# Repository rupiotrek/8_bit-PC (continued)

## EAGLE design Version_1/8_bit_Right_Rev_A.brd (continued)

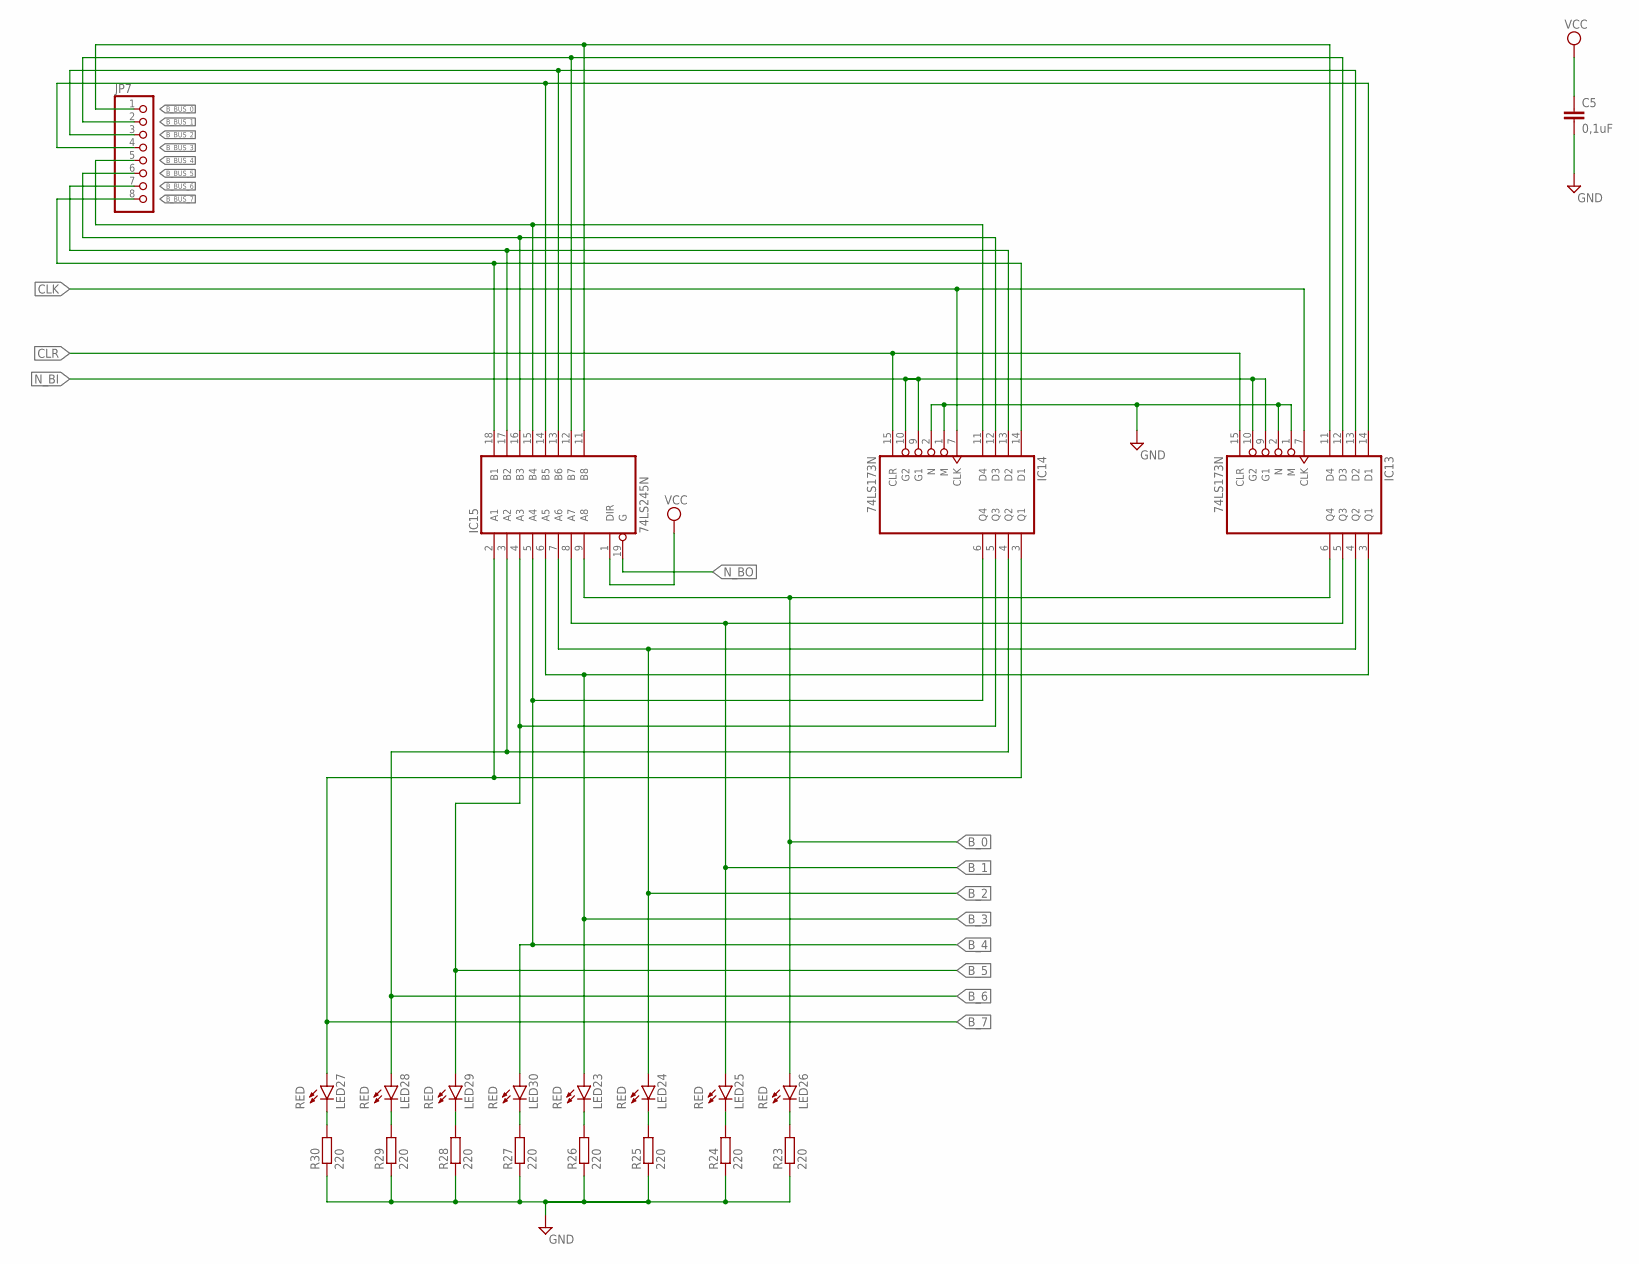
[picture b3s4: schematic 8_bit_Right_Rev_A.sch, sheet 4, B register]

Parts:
C5: 0,1uF; C025-030X050
IC13, IC14: 74LS173N; DIL16
IC15: 74LS245N; DIL20
JP7: PINHD-1X8; 1X08
LED23, LED24, LED25, LED26, LED27, LED28, LED29, LED30: RED; LED5MM
R23, R24, R25, R26, R27, R28, R29, R30: 220; 0207/10

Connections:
B_0: IC13.6 (Q4), IC15.9 (A8), LED26.A; also elsewhere on the board
B_1: IC13.5 (Q3), IC15.8 (A7), LED25.A; also elsewhere on the board
B_2: IC13.4 (Q2), IC15.7 (A6), LED24.A; also elsewhere on the board
B_3: IC13.3 (Q1), IC15.6 (A5), LED23.A; also elsewhere on the board
B_4: IC14.6 (Q4), IC15.5 (A4), LED30.A; also elsewhere on the board
B_5: IC14.5 (Q3), IC15.4 (A3), LED29.A; also elsewhere on the board
B_6: IC14.4 (Q2), IC15.3 (A2), LED28.A; also elsewhere on the board
B_7: IC14.3 (Q1), IC15.2 (A1), LED27.A; also elsewhere on the board
B_BUS_0: IC13.11 (D4), IC15.11 (B8), JP7.1
B_BUS_1: IC13.12 (D3), IC15.12 (B7), JP7.2
B_BUS_2: IC13.13 (D2), IC15.13 (B6), JP7.3
B_BUS_3: IC13.14 (D1), IC15.14 (B5), JP7.4
B_BUS_4: IC14.11 (D4), IC15.15 (B4), JP7.5
B_BUS_5: IC14.12 (D3), IC15.16 (B3), JP7.6
B_BUS_6: IC14.13 (D2), IC15.17 (B2), JP7.7
B_BUS_7: IC14.14 (D1), IC15.18 (B1), JP7.8
CLK: IC13.7 (CLK), IC14.7 (CLK); also elsewhere on the board
CLR: IC13.15 (CLR), IC14.15 (CLR); also elsewhere on the board
GND: C5.2, IC13.1 (M), IC13.2 (N), IC13.8 (GND), IC14.1 (M), IC14.2 (N), IC14.8 (GND), IC15.10 (GND), R23.1, R24.1, R25.1, R26.1, R27.1, R28.1, R29.1, R30.1; also elsewhere on the board
GND9: LED26.K (C), R23.2
GND10: LED25.K (C), R24.2
GND11: LED24.K (C), R25.2
GND12: LED23.K (C), R26.2
GND13: LED30.K (C), R27.2
GND14: LED29.K (C), R28.2
GND15: LED28.K (C), R29.2
GND16: LED27.K (C), R30.2
N_BI: IC13.9 (G1), IC13.10 (G2), IC14.9 (G1), IC14.10 (G2); also elsewhere on the board
N_BO: IC15.19 (G)
VCC: C5.1, IC13.16 (VCC), IC14.16 (VCC), IC15.1 (DIR), IC15.20 (VCC); also elsewhere on the board

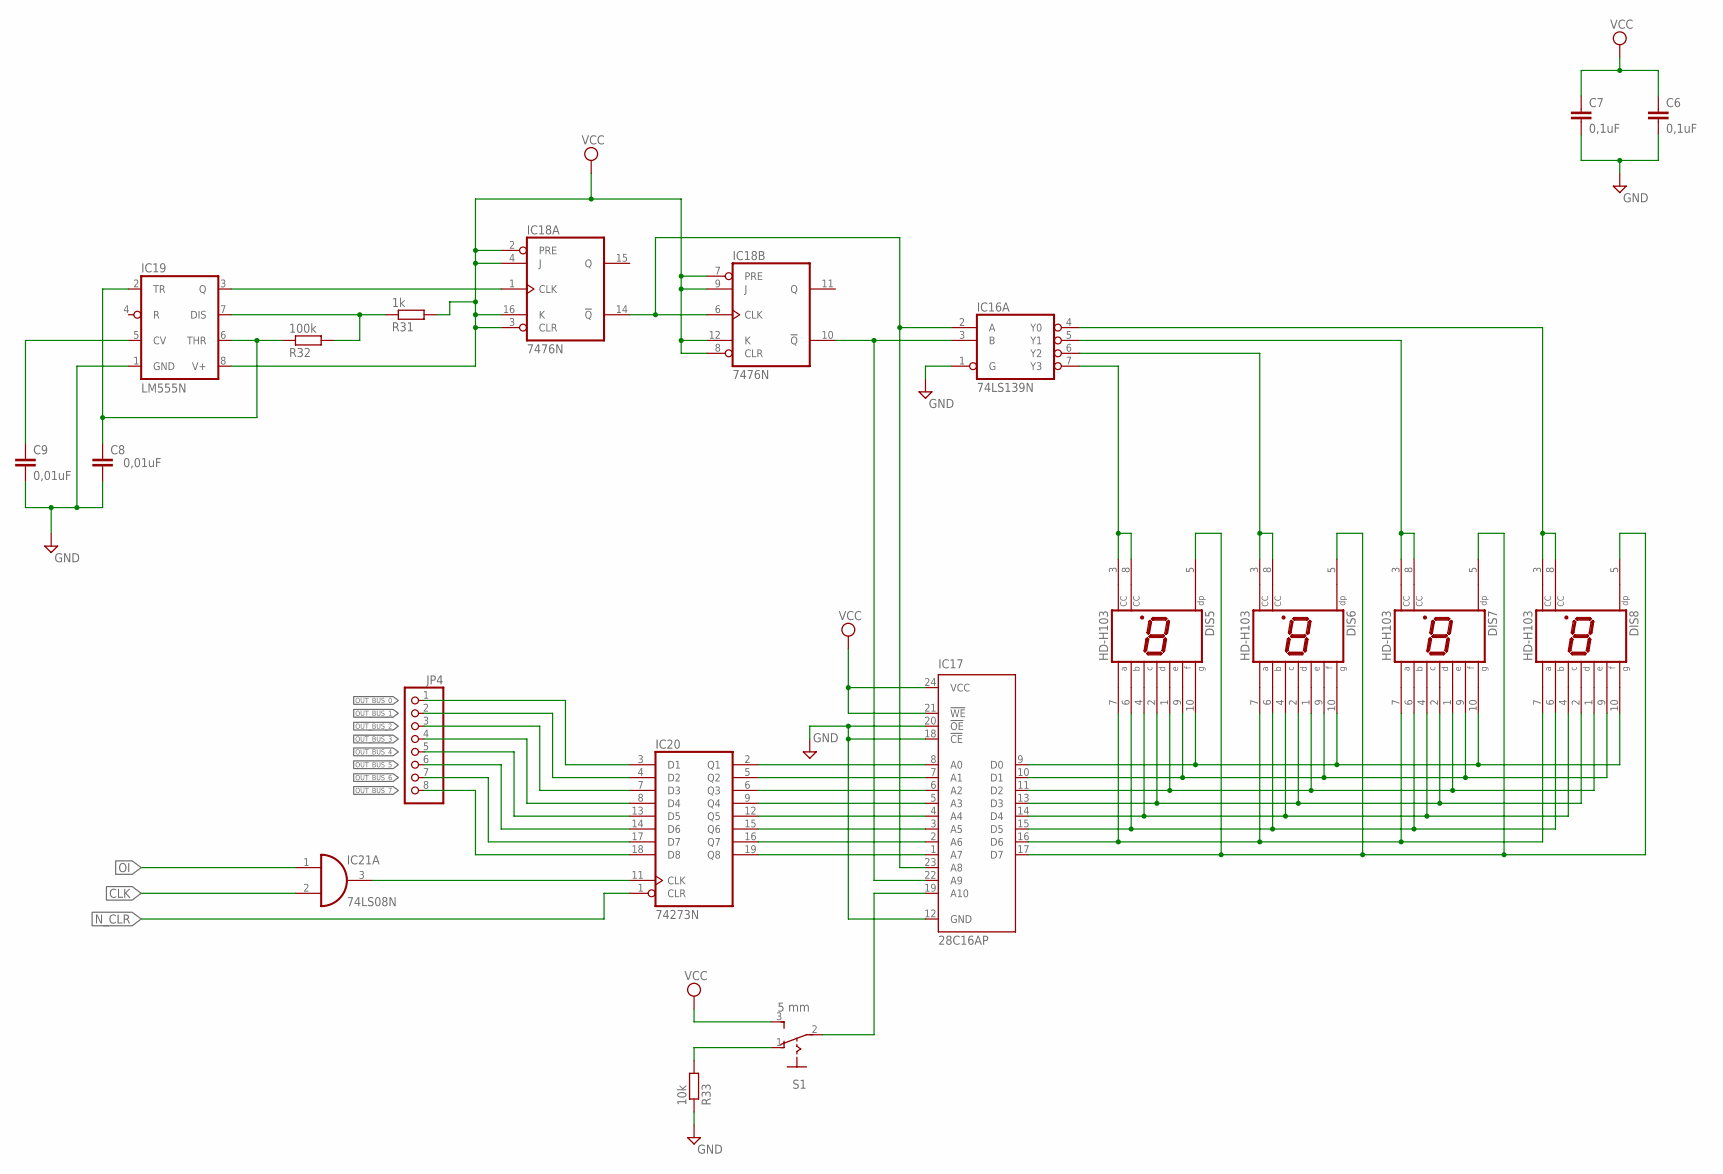
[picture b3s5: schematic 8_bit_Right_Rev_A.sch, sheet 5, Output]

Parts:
C6, C7: 0,1uF; C025-030X050
C8, C9: 0,01uF; C025-030X050
DIS5, DIS6, DIS7, DIS8: HD-H103; HDSP-M
IC16: 74LS139N; DIL16
IC17: 28C16AP; DIL24-6
IC18: 7476N; DIL16
IC19: LM555N; DIL08
IC20: 74273N; DIL20
IC21: 74LS08N; DIL14
JP4: PINHD-1X8; 1X08
R31: 1k; 0207/10
R32: 100k; 0207/10
R33: 10k; 0207/10
S1: 5 mm; 255SB

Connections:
CLK: IC21.2 (I1); also elsewhere on the board
GND: C6.2, C7.2, C8.2, C9.2, IC16.1 (G), IC16.8 (GND), IC17.12 (GND), IC17.18 (!CE), IC17.20 (!OE), IC18.13 (GND), IC19.1 (GND), IC20.10 (GND), IC21.7 (GND), R33.1; also elsewhere on the board
unnamed: IC17.8 (A0), IC20.2 (Q1)
unnamed: IC17.7 (A1), IC20.5 (Q2)
unnamed: IC17.6 (A2), IC20.6 (Q3)
unnamed: IC17.5 (A3), IC20.9 (Q4)
unnamed: IC17.4 (A4), IC20.12 (Q5)
unnamed: IC17.3 (A5), IC20.15 (Q6)
unnamed: IC17.2 (A6), IC20.16 (Q7)
unnamed: IC17.1 (A7), IC20.19 (Q8)
unnamed: DIS5.5 (DP), DIS6.5 (DP), DIS7.5 (DP), DIS8.5 (DP), IC17.17 (D7)
unnamed: DIS5.7 (A), DIS6.7 (A), DIS7.7 (A), DIS8.7 (A), IC17.16 (D6)
unnamed: DIS5.6 (B), DIS6.6 (B), DIS7.6 (B), DIS8.6 (B), IC17.15 (D5)
unnamed: DIS5.4 (C), DIS6.4 (C), DIS7.4 (C), DIS8.4 (C), IC17.14 (D4)
unnamed: DIS5.2 (D), DIS6.2 (D), DIS7.2 (D), DIS8.2 (D), IC17.13 (D3)
unnamed: DIS5.1 (E), DIS6.1 (E), DIS7.1 (E), DIS8.1 (E), IC17.11 (D2)
unnamed: DIS5.9 (F), DIS6.9 (F), DIS7.9 (F), DIS8.9 (F), IC17.10 (D1)
unnamed: DIS5.10 (G), DIS6.10 (G), DIS7.10 (G), DIS8.10 (G), IC17.9 (D0)
unnamed: DIS5.3 (CC), DIS5.8 (CC), IC16.7 (Y3)
unnamed: DIS6.3 (CC), DIS6.8 (CC), IC16.6 (Y2)
unnamed: DIS7.3 (CC), DIS7.8 (CC), IC16.5 (Y1)
unnamed: DIS8.3 (CC), DIS8.8 (CC), IC16.4 (Y0)
unnamed: IC16.3 (B), IC17.22 (A9), IC18.10 (!Q)
unnamed: IC16.2 (A), IC17.23 (A8), IC18.6 (CLK), IC18.14 (!Q)
unnamed: IC18.1 (CLK), IC19.3 (Q)
unnamed: IC19.7 (DIS), R31.1, R32.2
unnamed: C8.1, IC19.2 (TR), IC19.6 (THR), R32.1
unnamed: C9.1, IC19.5 (CV)
unnamed: IC20.11 (CLK), IC21.3 (O)
unnamed: IC17.19 (A10), S1.2
unnamed: R33.2, S1.1 (O)
N_CLR: IC20.1 (CLR); also elsewhere on the board
OI: IC21.1 (I0); also elsewhere on the board
OUT_BUS_0: IC20.3 (D1), JP4.1
OUT_BUS_1: IC20.4 (D2), JP4.2
OUT_BUS_2: IC20.7 (D3), JP4.3
OUT_BUS_3: IC20.8 (D4), JP4.4
OUT_BUS_4: IC20.13 (D5), JP4.5
OUT_BUS_5: IC20.14 (D6), JP4.6
OUT_BUS_6: IC20.17 (D7), JP4.7
OUT_BUS_7: IC20.18 (D8), JP4.8
VCC: C6.1, C7.1, IC16.16 (VCC), IC17.21 (!WE), IC17.24 (VCC), IC18.2 (PRE), IC18.3 (CLR), IC18.4 (J), IC18.5 (VCC), IC18.7 (PRE), IC18.8 (CLR), IC18.9 (J), IC18.12 (K), IC18.16 (K), IC19.8 (V+), IC20.20 (VCC), IC21.14 (VCC), R31.2, S1.3 (S); also elsewhere on the board

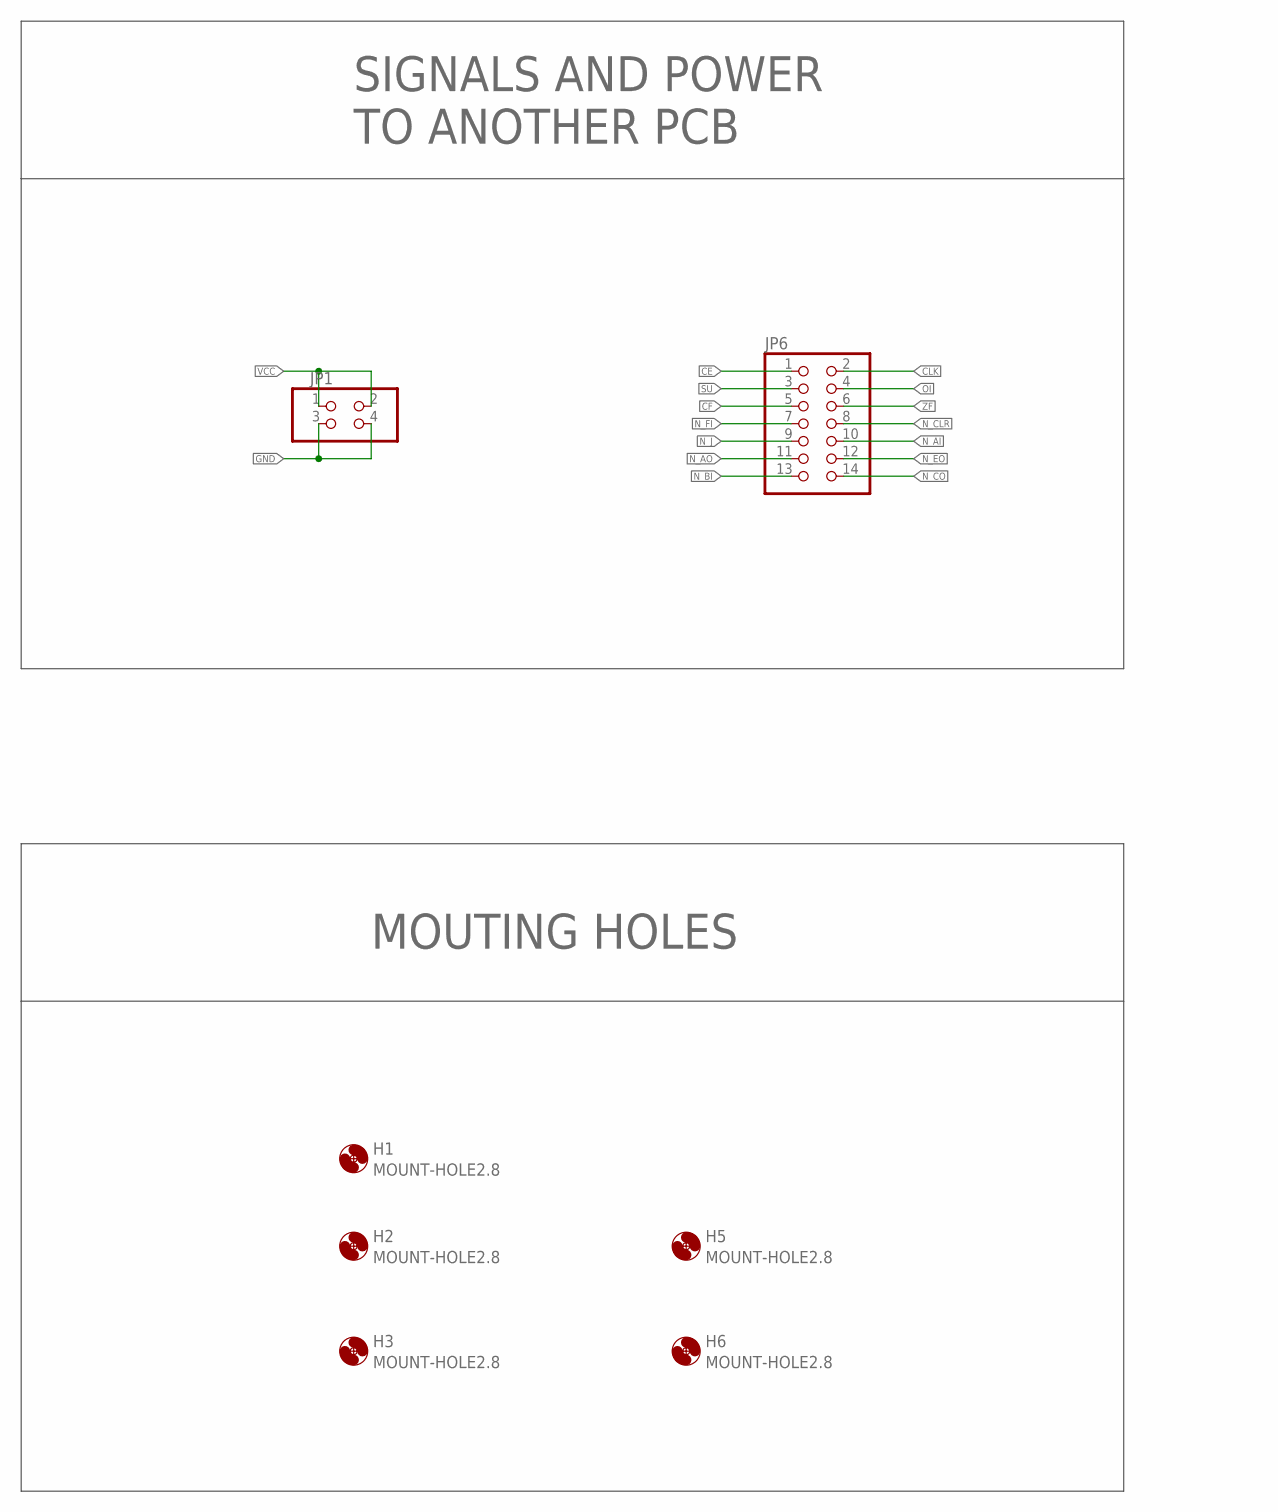
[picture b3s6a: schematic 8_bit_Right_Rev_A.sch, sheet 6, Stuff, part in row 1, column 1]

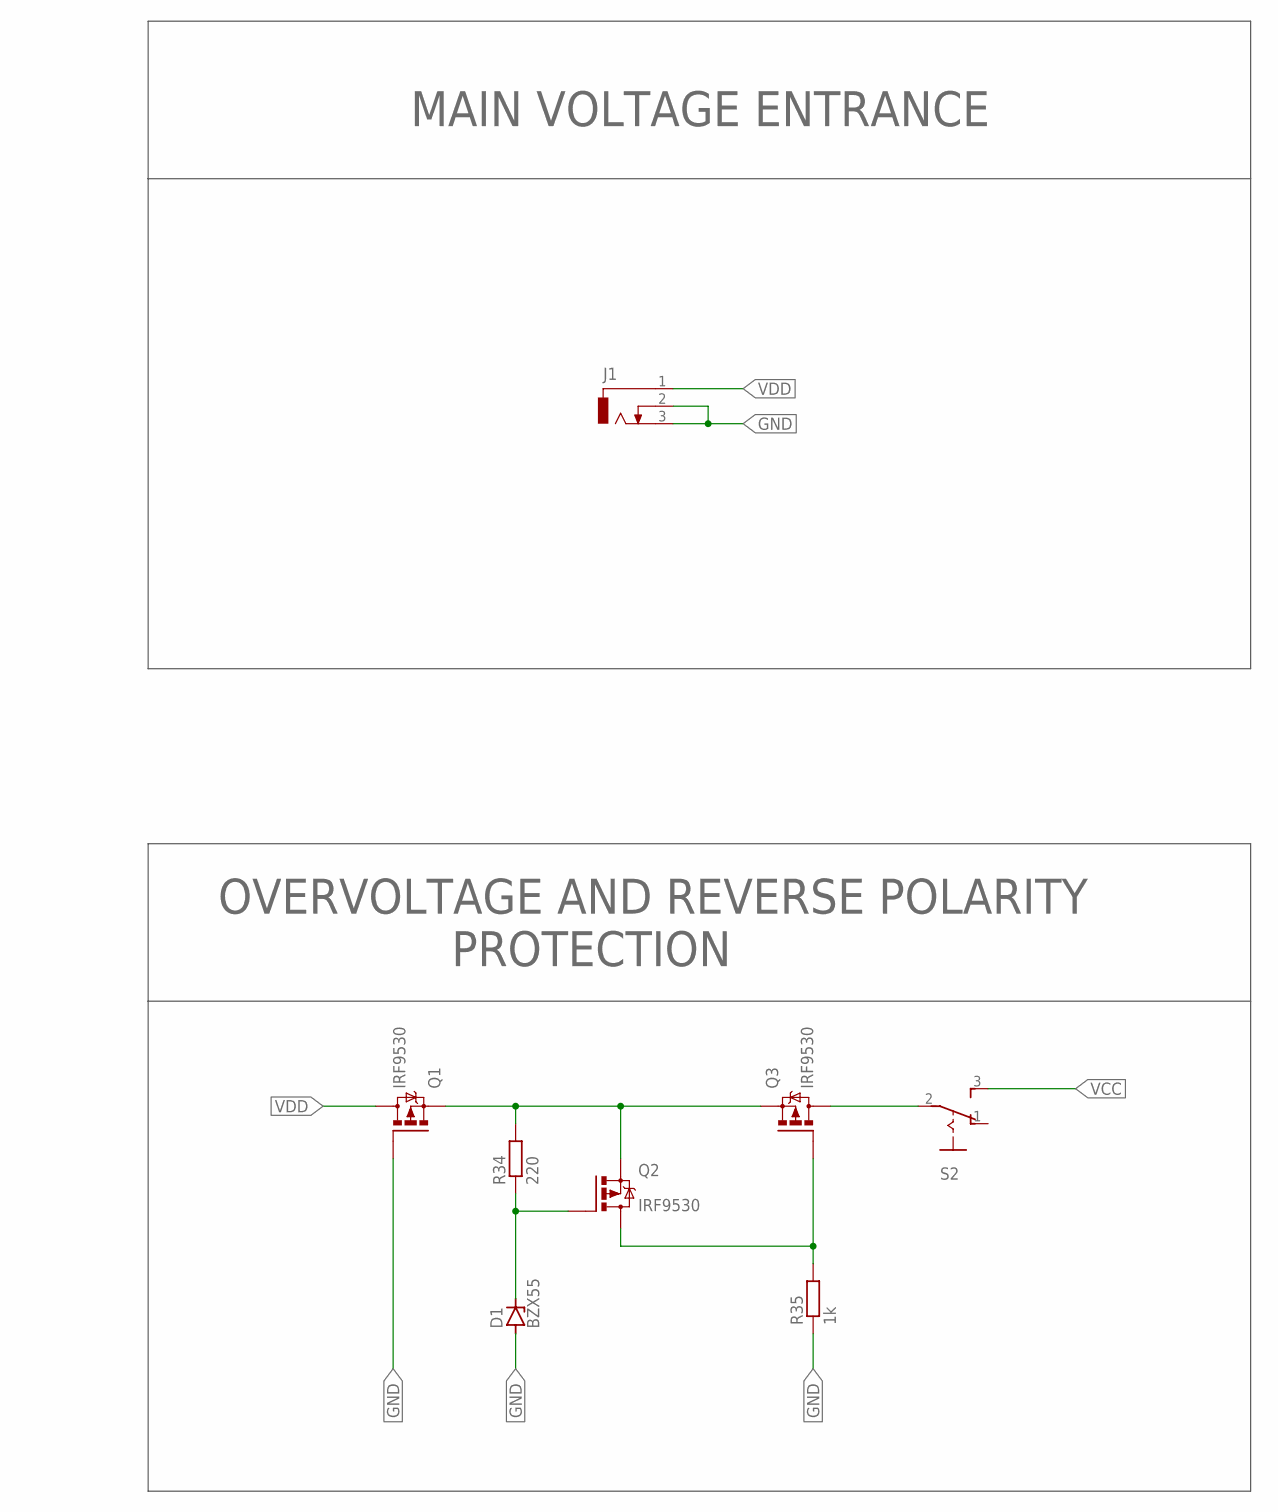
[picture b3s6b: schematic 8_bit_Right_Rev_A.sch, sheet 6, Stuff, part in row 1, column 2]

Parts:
D1: BZX55; DO35Z10
H1, H2, H3, H5, H6: MOUNT-HOLE2.8; 2,8
J1: DCJ0303
JP1: PINHD-2X2; 2X02
JP6: PINHD-2X7; 2X07
Q1, Q2, Q3: IRF9530; TO220BV
R34: 220; 0207/10
R35: 1k; 0207/10
S2: 255SB

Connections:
CE: JP6.1; also elsewhere on the board
CF: JP6.5; also elsewhere on the board
CLK: JP6.2; also elsewhere on the board
GND: D1.A, J1.2, J1.3, JP1.3, JP1.4, Q1.G, R35.1; also elsewhere on the board
unnamed: Q1.S, Q2.S, Q3.S, R34.2
unnamed: D1.C, Q2.G, R34.1
unnamed: Q3.D, S2.2
unnamed: Q2.D, Q3.G, R35.2
N_AI: JP6.10; also elsewhere on the board
N_AO: JP6.11; also elsewhere on the board
N_BI: JP6.13; also elsewhere on the board
N_CLR: JP6.8; also elsewhere on the board
N_CO: JP6.14; also elsewhere on the board
N_EO: JP6.12; also elsewhere on the board
N_FI: JP6.7; also elsewhere on the board
N_J: JP6.9; also elsewhere on the board
OI: JP6.4; also elsewhere on the board
SU: JP6.3; also elsewhere on the board
VCC: JP1.1, JP1.2, S2.3 (S); also elsewhere on the board
VDD: J1.1, Q1.D
ZF: JP6.6; also elsewhere on the board

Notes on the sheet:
MAIN VOLTAGE ENTRANCE
OVERVOLTAGE AND REVERSE POLARITY PROTECTION
MOUTING HOLES
SIGNALS AND POWER TO ANOTHER PCB

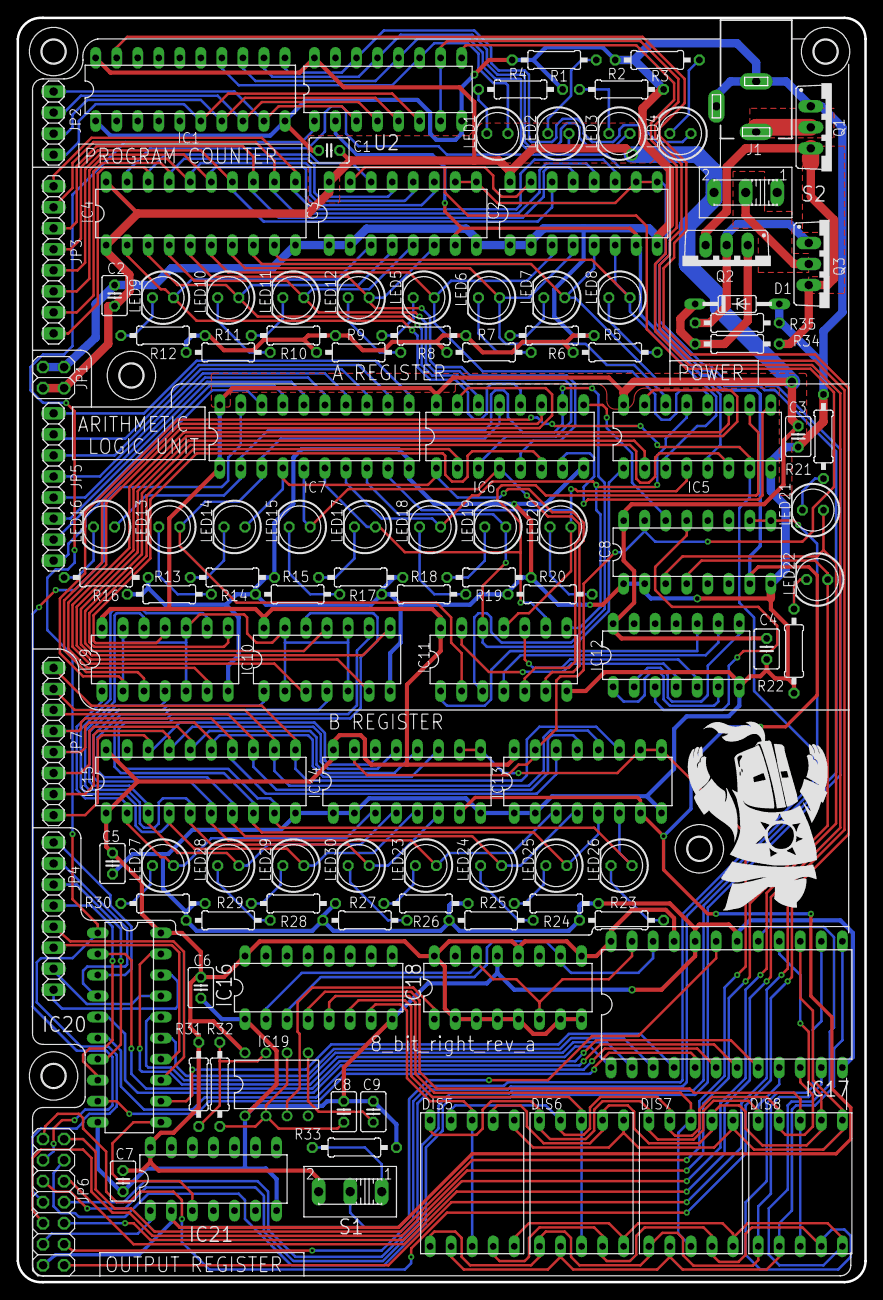
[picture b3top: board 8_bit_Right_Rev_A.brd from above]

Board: 2 copper layers, 102.4 x 152.7 mm, 121 parts (1 on the bottom side), 162 nets.

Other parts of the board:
U$1: SOLAIRE
U$2: MUELLTONNE_10.00

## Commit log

2020-04-09 Vesrsion 1 Left part of the PC
2020-04-09 Version 1 Middle part of the PC
2020-04-09 Version 1 Right part of the PC
2020-04-09 Create README.md
    First description
2020-04-09 Create .gitignore
    First gitignore file
2020-04-09 First gitignore file
2020-04-09 First README file
2020-04-09 Reformatted license
2020-04-10 Full BOM for 3 PCB
2020-04-10 Gerber files
2020-04-10 updated readme about ver1
2020-04-10 Improved BOM
2020-04-10 Sorterd stuff
2020-04-15 Fixed DRC problems
2020-04-15 Screen of the board
2020-04-15 Trash image on the other side
